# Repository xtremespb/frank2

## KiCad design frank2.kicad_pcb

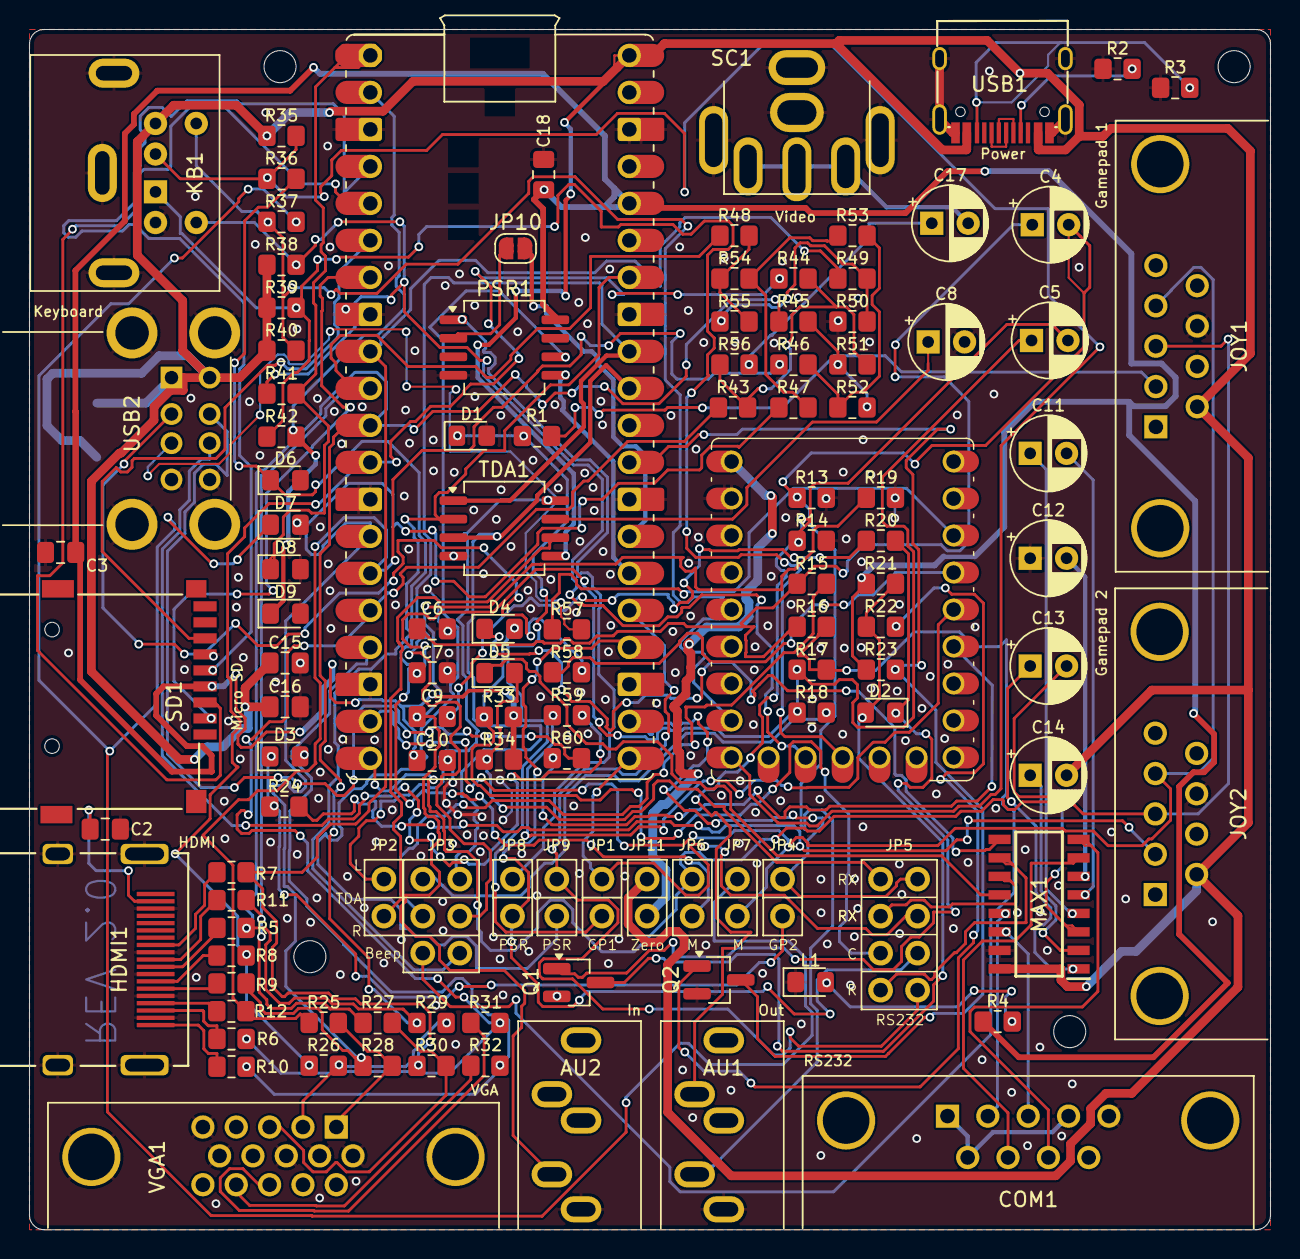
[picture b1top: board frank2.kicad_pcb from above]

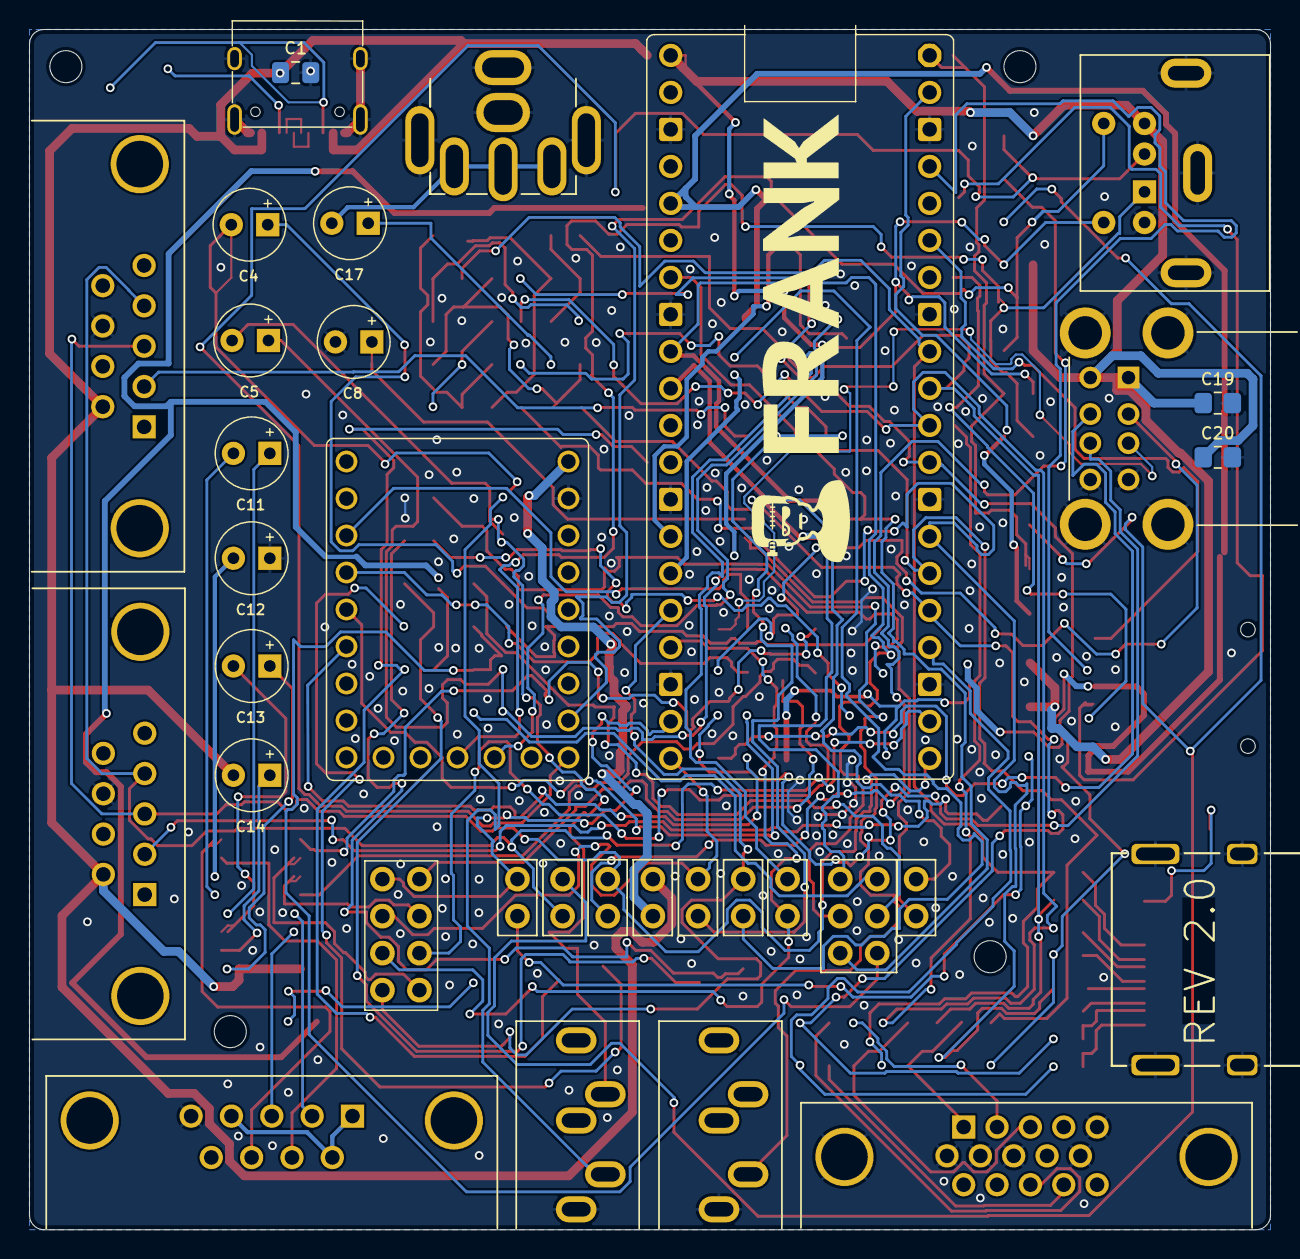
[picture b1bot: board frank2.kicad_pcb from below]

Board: 2 copper layers, 85.2 x 82.4 mm, 124 parts (3 on the bottom side), 110 nets.

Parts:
AU1: AUDIO OUT; Medved_Jack_3.5mm_CUI_SJ1-3535NG_Horizontal
AU2: AUDIO IN; Medved_Jack_3.5mm_CUI_SJ1-3535NG_Horizontal
C1: 10u; Medved_C_0805
C2, C3, C9, C10, C15, C16, C18: 0.1u; Medved_C_0805
C4, C5, C8: 10u; Medved_CP_Radial_D5.0mm_P2.50mm
C6, C7: 10n; Medved_C_0805
C11, C12, C13, C14: 1u; Medved_CP_Radial_D5.0mm_P2.50mm
C17: 220u; Medved_CP_Radial_D5.0mm_P2.50mm
C19, C20: 10u; Medved_R_0805
COM1: RS232; DB9
D1, D3, D6, D7, D8, D9: 3V3; Medved_D_0805
D2: 4148; Medved_D_0805
D4, D5: 1N4148; Medved_D_0805
H1, H2, H3, H4: MountingHole; Medved_MountingHole_V2
HDMI1: HDMI
JOY1, JOY2: Joystick; DB9
JP1, JP4, JP6, JP7, JP8, JP9, JP11: RP ZERO +5V Jumper; Medved_PinHeader_1x02_P2.54mm_Vertical_R
JP2: I2S; Medved_PinHeader_1x02
JP3: Audio Jumpers; Medved_JMP_2x03
JP5: RS232 Jumpers; Medved_PinHeader_2x04_P2.54mm_Vertical
JP10: JMP PSRAM; SolderJumper-2_P1.3mm_Open_RoundedPad1.0x1.5mm
KB1: PS/2; Connector_Mini-DIN_Female_6Pin_2rows
L1: GREEN; Medved_L_0805
MAX1: MAX232CSE+; SOIC127P600X175-16N
PSR1: PSRAM; SO-8_5.3x6.2mm_P1.27mm
Q1, Q2: BC850; SOT-23_Handsoldering
R1, R15, R18, R23, R24, R28, R29, R30, R35, R38, R39, R40: 1k; Medved_R_0805
R2, R3: 5.1K; Medved_R_0805
R4, R33, R34: 1K; Medved_R_0805
R5, R6, R7, R8, R9, R10, R11, R12, R44, R45, R46, R47, R48, R49: 270R; Medved_R_0805
R13, R14, R25, R26, R27: 330R; Medved_R_0805
R16, R17: 2k; Medved_R_0805
R19, R31, R32, R36, R37, R41, R42: 100R; Medved_R_0805
R20, R21, R22: 10k; Medved_R_0805
R43: 750R*; Medved_R_0805
R50: 300R; Medved_R_0805
R51, R52, R53, R54, R55: 150R; Medved_R_0805
R56: 51R*; Medved_R_0805
R57, R58, R59, R60: 22R; Medved_R_0805
RP1: RP2040 Pico; Raspberry_Pi_Pico_SMT_THT_MOD_2
RP2: RP 2040 Zero; rp2040-zero-tht
SC1: VIDEO (Soft Composite); AV_MOD_III-8.4-5
SD1: Micro SD; Medved_SD_Card
TDA1: TDA1387T; SO-8_5.3x6.2mm_P1.27mm
USB1: USB Type C; USB-TYPE-C-31-M-12_lib2
USB2: USB_A_Stacked; Medved_USB_A_CUI_UJ2-ADH-TH_Horizontal_Stacked
VGA1: VGA; Medved_DSUB-15-HD_Female_Horizontal

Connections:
+3V3: C3.2, C10.1, C18.1, PSR1.8 (VCC), R4.2, R21.1, R23.1, R33.2, R34.2, RP1.36 (3V3_OUT), SD1.4 (VDD)
/Audio/BEEP_OUT: JP3.5, R16.2, R17.2
/Audio/FLT: C8.1, TDA1.7 (FLT)
/Audio/L: AU1.T, C4.2, R13.1
/Audio/LEFT_OUT: JP3.3, R15.2
/Audio/LEFT_TDA: JP2.2, TDA1.6 (A_LEFT)
/Audio/LOAD_IN: AU2.T, C9.1, R19.1
/Audio/R: AU1.R, C5.2, R14.1
/Audio/RIGHT_OUT: JP3.1, R18.2
/Audio/RIGHT_TDA: JP2.1, TDA1.8 (A_RIGHT)
/Composite Video/CVBS: C17.2, SC1.1
/GPIO0: D8.1 (K), R41.2, RP1.1 (GP0)
/GPIO1: D9.1 (K), R42.2, RP1.2 (GP1)
/GPIO2: RP1.4 (GP2), SD1.5 (CLK)
/GPIO3: RP1.5 (GP3), SD1.3 (CMD)
/GPIO4: RP1.6 (GP4), SD1.7 (DAT0)
/GPIO5: RP1.7 (GP5), SD1.2 (DAT3/CD)
/GPIO6: R7.2, R30.1, R49.1, RP1.9 (GP6)
/GPIO7: R11.2, R27.1, R48.1, RP1.10 (GP7)
/GPIO8: R5.2, R29.1, R45.1, RP1.11 (GP8)
/GPIO9: R8.2, R26.1, R44.1, RP1.12 (GP9)
/GPIO10: R9.2, R28.1, R47.1, RP1.14 (GP10)
/GPIO11: R12.2, R25.1, R46.1, RP1.15 (GP11)
/GPIO12: R6.2, R31.2, R43.1, RP1.16 (GP12)
/GPIO13: R10.2, R32.2, RP1.17 (GP13)
/GPIO14: JOY1.4, JOY2.4, JP7.2 (B), RP1.19 (GP14)
/GPIO15: JOY1.3, JOY2.3, JP6.1 (A), RP1.20 (GP15)
/GPIO16: JP1.1 (A), JP5.4, RP1.21 (GP16)
/GPIO17: JP4.1 (A), JP5.2, RP1.22 (GP17)
/GPIO18: JP5.6, JP8.2 (B), RP1.24 (GP18)
/GPIO19: JP5.8, JP9.1 (A), RP1.25 (GP19)
/GPIO20: PSR1.5 (SI/SIO), RP1.26 (GP20)
/GPIO21: JP10.2 (B), RP1.27 (GP21)
/GPIO22: Q2.3 (C), R23.2, RP1.29 (GP22)
/GPIO26: JP3.2, RP1.31 (GP26_ADC0), TDA1.3 (DATA)
/GPIO27: JP3.4, RP1.32 (GP27_ADC1), TDA1.1 (SCLK)
/GPIO28: JP3.6, RP1.34 (GP28_ADC2), TDA1.2 (LRCK)
/Gamepad 1/J2_DATA: JOY1.2, R1.2
/Gamepad 2/J2_DATA: JOY2.2, R24.2
/HDMI/CLKN: HDMI1.12 (CLKN), R7.1
/HDMI/CLKP: HDMI1.10 (CLKP), R11.1
/HDMI/D0N: HDMI1.9 (D0N), R5.1
/HDMI/D0P: HDMI1.7 (D0P), R8.1
/HDMI/D1N: HDMI1.6 (D1N), R9.1
/HDMI/D1P: HDMI1.4 (D1P), R12.1
/HDMI/D2N: HDMI1.3 (D2N), R6.1
/HDMI/D2P: HDMI1.1 (D2P), R10.1
/HDMI/VBUS: C2.1, HDMI1.18 (+5V)
/Power/D+: USB1.6 (DP1), USB1.8 (DP2)
/Power/D-: USB1.5 (DN2), USB1.7 (DN1)
/RS232/C1+: C13.1, MAX1.1 (C1+)
/RS232/C1-: C13.2, MAX1.3 (C1-)
/RS232/C2+: C11.1, MAX1.4 (C2+)
/RS232/C2-: C11.2, MAX1.5 (C2-)
/RS232/CTS_IN: COM1.7, MAX1.7 (T2OUT)
/RS232/CTS_MAX: D4.1 (K), MAX1.9 (R2OUT)
/RS232/CTS_PICO: D4.2 (A), JP5.5, R33.1
/RS232/RTS_IN: COM1.8, MAX1.8 (R2IN)
/RS232/RTS_PICO: JP5.7, MAX1.10 (T2IN)
/RS232/RX_IN: COM1.3, MAX1.14 (T1OUT)
/RS232/RX_MAX: D5.1 (K), MAX1.12 (R1OUT)
/RS232/RX_PICO: D5.2 (A), JP5.1, R34.1
/RS232/TX_IN: COM1.2, MAX1.13 (R1IN)
/RS232/TX_PICO: JP5.3, MAX1.11 (T1IN)
/RS232/V+: C14.1, MAX1.2 (V+)
/RS232/V-: C12.2, MAX1.6 (V-)
/VGA/VGA_BH: R27.2, R30.2, VGA1.3
/VGA/VGA_GH: R26.2, R29.2, VGA1.2
/VGA/VGA_HS: R31.1, VGA1.13
/VGA/VGA_RH: R25.2, R28.2, VGA1.1
/VGA/VGA_VS: R32.1, VGA1.14
/ZGPIO2: R57.1, RP2.3 (2)
/ZGPIO3: R58.1, RP2.4 (3)
/ZGPIO4: R59.1, RP2.5 (4)
/ZGPIO5: R60.1, RP2.6 (5)
/ZGPIO11: KB1.1, R39.2, R42.1, RP2.12 (11)
/ZGPIO12: KB1.5, R38.2, R41.1, RP2.13 (12)
/ZGPIO14: KB1.2, R35.2, R36.1, RP2.15 (14)
/ZGPIO15: KB1.6, R37.1, R40.2, RP2.16 (15)
GND: AU1.S, AU2.S, C1.2, C2.2, C3.1, C6.2, C7.2, C8.2, C10.2, C12.1, C15.2, C16.2, C18.2, C19.2, C20.2, COM1.5, D1.2 (A), D3.2 (A), D6.2 (A), D7.2 (A), D8.2 (A), D9.2 (A), HDMI1.2 (G_D2), HDMI1.5 (G_D1), HDMI1.8 (G_D0), HDMI1.11 (G_CLK), HDMI1.17 (G_DDC/CEC), HDMI1.20 (SHIELD1), HDMI1.21 (SHIELD2), HDMI1.22 (SHIELD3), HDMI1.23 (SHIELD4), JOY1.8, JOY2.8, KB1.3, L1.1 (K), MAX1.15 (GND), PSR1.4 (VSS), Q1.2 (E), Q2.2 (E), R2.1, R3.1, R13.2, R14.2, R19.2, R50.1, RP1.3 (GND), RP1.8 (GND), RP1.13 (GND), RP1.18 (GND), RP1.23 (GND), RP1.28 (GND), RP1.33 (GND_AGND), RP1.38 (GND), RP2.22 (GND), SC1.2, SD1.6 (VSS), TDA1.4 (AGND), USB1.1 (GND), USB1.12 (GND), USB1.13 (SHIELD), USB2.4 (GND1), USB2.8 (GND2), USB2.9 (Shield), VGA1.0, VGA1.5, VGA1.6, VGA1.7, VGA1.8, VGA1.10
unnamed: C4.1, C6.1, R15.1, R16.1
unnamed: C5.1, C7.1, R17.1, R18.1
unnamed: C9.2, R20.1
unnamed: C17.1, R56.2
unnamed: COM1.1, COM1.4, COM1.6
unnamed: D1.1 (K), JP1.2 (B), R1.1
unnamed: D2.2 (A), Q1.3 (C), R21.2, R22.1
unnamed: D2.1 (K), Q1.1 (B), R20.2
unnamed: D3.1 (K), JP4.2 (B), R24.1
unnamed: D6.1 (K), JP6.2 (B), R36.2
unnamed: D7.1 (K), JP7.1 (A), R37.2
unnamed: JP8.1 (A), PSR1.1 (~CE)
unnamed: JP9.2 (B), PSR1.6 (SCLK)
unnamed: JP10.1 (A), PSR1.2 (SO/SIO)
unnamed: JP11.2 (B), RP2.23 (5V)
unnamed: L1.2 (A), R4.1
unnamed: Q2.1 (B), R22.2
unnamed: R43.2, R44.2, R51.2, R56.1
unnamed: R45.2, R51.1, R52.2
unnamed: R46.2, R52.1, R53.2
unnamed: R47.2, R53.1, R54.2
unnamed: R48.2, R54.1, R55.2
unnamed: R49.2, R50.2, R55.1
unnamed: R2.2, USB1.4 (CC1)
unnamed: R3.2, USB1.10 (CC2)
unnamed: R57.2, USB2.3 (D1+)
unnamed: R58.2, USB2.2 (D1-)
unnamed: R59.2, USB2.7 (D2+)
unnamed: R60.2, USB2.6 (D2-)
VBUS: C1.1, C14.2, C15.1, C16.1, C19.1, C20.1, JOY1.6, JOY2.6, JP11.1 (A), KB1.4, MAX1.16 (VCC), R35.1, R38.1, R39.1, R40.1, RP1.40 (VBUS), TDA1.5 (VA), USB1.2 (VBUS), USB1.11 (VBUS), USB2.1 (VBUS1), USB2.5 (VBUS2)

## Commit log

2024-11-21 HW Rev 1.0
2024-11-21 Gerber added
2024-11-22 Cleanup
2024-12-15 Updated HW
2024-12-15 HW Rev 2.0
